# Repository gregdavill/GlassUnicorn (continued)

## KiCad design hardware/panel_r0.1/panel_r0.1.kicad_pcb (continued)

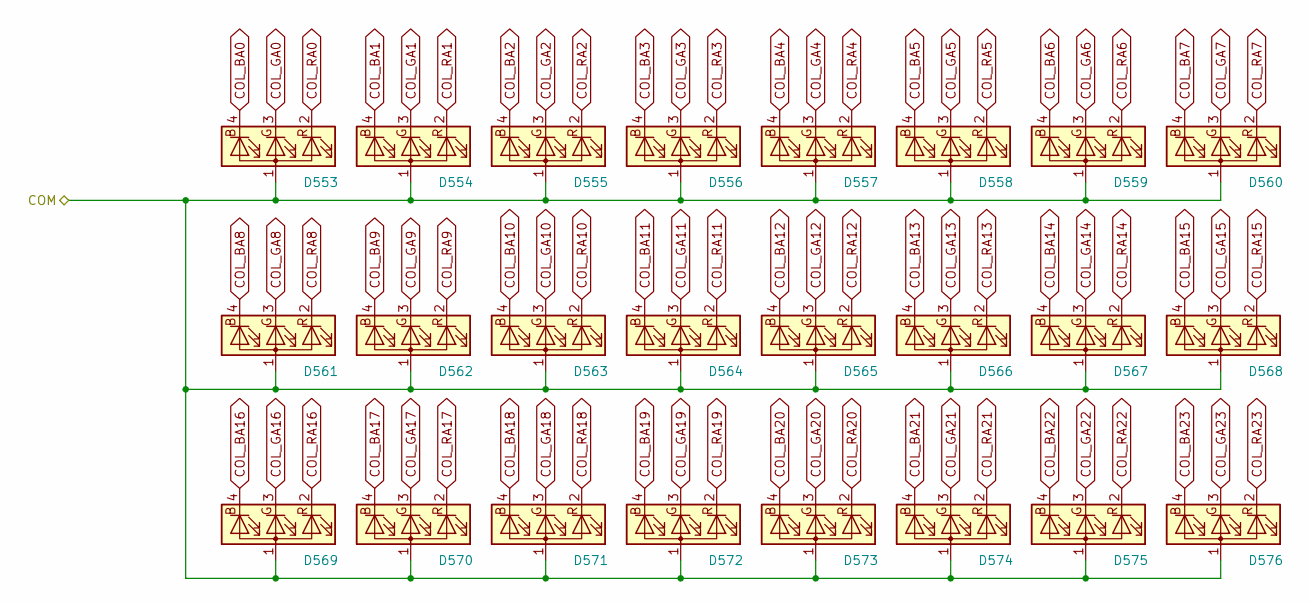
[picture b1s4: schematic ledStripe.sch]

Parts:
D1, D2, D3, D4, D5, D6, D7, D8, D9, D10, D11, D12, D13, D14, D15, D16, D17, D18, D19, D20, D21, D22, D23, D24: LED_ARGB; led_rbag_2121_dense

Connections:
/ledArray/sheet5D7371BF/COM: D1.1 (A), D2.1 (A), D3.1 (A), D4.1 (A), D5.1 (A), D6.1 (A), D7.1 (A), D8.1 (A), D9.1 (A), D10.1 (A), D11.1 (A), D12.1 (A), D13.1 (A), D14.1 (A), D15.1 (A), D16.1 (A), D17.1 (A), D18.1 (A), D19.1 (A), D20.1 (A), D21.1 (A), D22.1 (A), D23.1 (A), D24.1 (A); also elsewhere on the board
COL_BA0: D1.4 (BK); also elsewhere on the board
COL_BA1: D2.4 (BK); also elsewhere on the board
COL_BA2: D3.4 (BK); also elsewhere on the board
COL_BA3: D4.4 (BK); also elsewhere on the board
COL_BA4: D5.4 (BK); also elsewhere on the board
COL_BA5: D6.4 (BK); also elsewhere on the board
COL_BA6: D7.4 (BK); also elsewhere on the board
COL_BA7: D8.4 (BK); also elsewhere on the board
COL_BA8: D9.4 (BK); also elsewhere on the board
COL_BA9: D10.4 (BK); also elsewhere on the board
COL_BA10: D11.4 (BK); also elsewhere on the board
COL_BA11: D12.4 (BK); also elsewhere on the board
COL_BA12: D13.4 (BK); also elsewhere on the board
COL_BA13: D14.4 (BK); also elsewhere on the board
COL_BA14: D15.4 (BK); also elsewhere on the board
COL_BA15: D16.4 (BK); also elsewhere on the board
COL_BA16: D17.4 (BK); also elsewhere on the board
COL_BA17: D18.4 (BK); also elsewhere on the board
COL_BA18: D19.4 (BK); also elsewhere on the board
COL_BA19: D20.4 (BK); also elsewhere on the board
COL_BA20: D21.4 (BK); also elsewhere on the board
COL_BA21: D22.4 (BK); also elsewhere on the board
COL_BA22: D23.4 (BK); also elsewhere on the board
COL_BA23: D24.4 (BK); also elsewhere on the board
COL_GA0: D1.3 (GK); also elsewhere on the board
COL_GA1: D2.3 (GK); also elsewhere on the board
COL_GA2: D3.3 (GK); also elsewhere on the board
COL_GA3: D4.3 (GK); also elsewhere on the board
COL_GA4: D5.3 (GK); also elsewhere on the board
COL_GA5: D6.3 (GK); also elsewhere on the board
COL_GA6: D7.3 (GK); also elsewhere on the board
COL_GA7: D8.3 (GK); also elsewhere on the board
COL_GA8: D9.3 (GK); also elsewhere on the board
COL_GA9: D10.3 (GK); also elsewhere on the board
COL_GA10: D11.3 (GK); also elsewhere on the board
COL_GA11: D12.3 (GK); also elsewhere on the board
COL_GA12: D13.3 (GK); also elsewhere on the board
COL_GA13: D14.3 (GK); also elsewhere on the board
COL_GA14: D15.3 (GK); also elsewhere on the board
COL_GA15: D16.3 (GK); also elsewhere on the board
COL_GA16: D17.3 (GK); also elsewhere on the board
COL_GA17: D18.3 (GK); also elsewhere on the board
COL_GA18: D19.3 (GK); also elsewhere on the board
COL_GA19: D20.3 (GK); also elsewhere on the board
COL_GA20: D21.3 (GK); also elsewhere on the board
COL_GA21: D22.3 (GK); also elsewhere on the board
COL_GA22: D23.3 (GK); also elsewhere on the board
COL_GA23: D24.3 (GK); also elsewhere on the board
COL_RA0: D1.2 (RK); also elsewhere on the board
COL_RA1: D2.2 (RK); also elsewhere on the board
COL_RA2: D3.2 (RK); also elsewhere on the board
COL_RA3: D4.2 (RK); also elsewhere on the board
COL_RA4: D5.2 (RK); also elsewhere on the board
COL_RA5: D6.2 (RK); also elsewhere on the board
COL_RA6: D7.2 (RK); also elsewhere on the board
COL_RA7: D8.2 (RK); also elsewhere on the board
COL_RA8: D9.2 (RK); also elsewhere on the board
COL_RA9: D10.2 (RK); also elsewhere on the board
COL_RA10: D11.2 (RK); also elsewhere on the board
COL_RA11: D12.2 (RK); also elsewhere on the board
COL_RA12: D13.2 (RK); also elsewhere on the board
COL_RA13: D14.2 (RK); also elsewhere on the board
COL_RA14: D15.2 (RK); also elsewhere on the board
COL_RA15: D16.2 (RK); also elsewhere on the board
COL_RA16: D17.2 (RK); also elsewhere on the board
COL_RA17: D18.2 (RK); also elsewhere on the board
COL_RA18: D19.2 (RK); also elsewhere on the board
COL_RA19: D20.2 (RK); also elsewhere on the board
COL_RA20: D21.2 (RK); also elsewhere on the board
COL_RA21: D22.2 (RK); also elsewhere on the board
COL_RA22: D23.2 (RK); also elsewhere on the board
COL_RA23: D24.2 (RK); also elsewhere on the board

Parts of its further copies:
D25, D26, D27, D28, D29, D30, D31, D32, D33, D34, D35, D36, D37, D38, D39, D40, D41, D42, D43, D44, D45, D46, D47, D48, D49, D50, D51, D52, D53, D54, D55, D56, D57, D58, D59, D60, D61, D62, D63, D64, D65, D66, D67, D68, D69, D70, D71, D72, D73, D74, D75, D76, D77, D78, D79, D80, D81, D82, D83, D84, D85, D86, D87, D88, D89, D90, D91, D92, D93, D94, D95, D96, D97, D98, D99, D100, D101, D102, D103, D104, D105, D106, D107, D108, D109, D110, D111, D112, D113, D114, D115, D116, D117, D118, D119, D120, D121, D122, D123, D124, D125, D126, D127, D128, D129, D130, D131, D132, D133, D134, D135, D136, D137, D138, D139, D140, D141, D142, D143, D144, D145, D146, D147, D148, D149, D150, D151, D152, D153, D154, D155, D156, D157, D158, D159, D160, D161, D162, D163, D164, D165, D166, D167, D168, D169, D170, D171, D172, D173, D174, D175, D176, D177, D178, D179, D180, D181, D182, D183, D184, D185, D186, D187, D188, D189, D190, D191, D192, D193, D194, D195, D196, D197, D198, D199, D200, D201, D202, D203, D204, D205, D206, D207, D208, D209, D210, D211, D212, D213, D214, D215, D216, D217, D218, D219, D220, D221, D222, D223, D224, D225, D226, D227, D228, D229, D230, D231, D232, D233, D234, D235, D236, D237, D238, D239, D240, D241, D242, D243, D244, D245, D246, D247, D248, D249, D250, D251, D252, D253, D254, D255, D256, D257, D258, D259, D260, D261, D262, D263, D264, D265, D266, D267, D268, D269, D270, D271, D272, D273, D274, D275, D276, D277, D278, D279, D280, D281, D282, D283, D284, D285, D286, D287, D288, D289, D290, D291, D292, D293, D294, D295, D296, D297, D298, D299, D300, D301, D302, D303, D304, D305, D306, D307, D308, D309, D310, D311, D312, D313, D314, D315, D316, D317, D318, D319, D320, D321, D322, D323, D324, D325, D326, D327, D328, D329, D330, D331, D332, D333, D334, D335, D336, D337, D338, D339, D340, D341, D342, D343, D344, D345, D346, D347, D348, D349, D350, D351, D352, D353, D354, D355, D356, D357, D358, D359, D360, D361, D362, D363, D364, D365, D366, D367, D368, D369, D370, D371, D372, D373, D374, D375, D376, D377, D378, D379, D380, D381, D382, D383, D384, D385, D386, D387, D388, D389, D390, D391, D392, D393, D394, D395, D396, D397, D398, D399, D400, D401, D402, D403, D404, D405, D406, D407, D408, D409, D410, D411, D412, D413, D414, D415, D416, D417, D418, D419, D420, D421, D422, D423, D424, D425, D426, D427, D428, D429, D430, D431, D432, D433, D434, D435, D436, D437, D438, D439, D440, D441, D442, D443, D444, D445, D446, D447, D448, D449, D450, D451, D452, D453, D454, D455, D456, D457, D458, D459, D460, D461, D462, D463, D464, D465, D466, D467, D468, D469, D470, D471, D472, D473, D474, D475, D476, D477, D478, D479, D480, D481, D482, D483, D484, D485, D486, D487, D488, D489, D490, D491, D492, D493, D494, D495, D496, D497, D498, D499, D500, D501, D502, D503, D504, D505, D506, D507, D508, D509, D510, D511, D512, D513, D514, D515, D516, D517, D518, D519, D520, D521, D522, D523, D524, D525, D526, D527, D528, D529, D530, D531, D532, D533, D534, D535, D536, D537, D538, D539, D540, D541, D542, D543, D544, D545, D546, D547, D548, D549, D550, D551, D552, D553, D554, D555, D556, D557, D558, D559, D560, D561, D562, D563, D564, D565, D566, D567, D568, D569, D570, D571, D572, D573, D574, D575, D576: LED_ARGB; led_rbag_2121_dense

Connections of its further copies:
/ledArray/sheet5D7D53E6/COM: D193.1 (A), D194.1 (A), D195.1 (A), D196.1 (A), D197.1 (A), D198.1 (A), D199.1 (A), D200.1 (A), D201.1 (A), D202.1 (A), D203.1 (A), D204.1 (A), D205.1 (A), D206.1 (A), D207.1 (A), D208.1 (A), D209.1 (A), D210.1 (A), D211.1 (A), D212.1 (A), D213.1 (A), D214.1 (A), D215.1 (A), D216.1 (A); also elsewhere on the board
/ledArray/sheet5D7D53F6/COM: D217.1 (A), D218.1 (A), D219.1 (A), D220.1 (A), D221.1 (A), D222.1 (A), D223.1 (A), D224.1 (A), D225.1 (A), D226.1 (A), D227.1 (A), D228.1 (A), D229.1 (A), D230.1 (A), D231.1 (A), D232.1 (A), D233.1 (A), D234.1 (A), D235.1 (A), D236.1 (A), D237.1 (A), D238.1 (A), D239.1 (A), D240.1 (A); also elsewhere on the board
/ledArray/sheet5D7D542A/COM: D289.1 (A), D290.1 (A), D291.1 (A), D292.1 (A), D293.1 (A), D294.1 (A), D295.1 (A), D296.1 (A), D297.1 (A), D298.1 (A), D299.1 (A), D300.1 (A), D301.1 (A), D302.1 (A), D303.1 (A), D304.1 (A), D305.1 (A), D306.1 (A), D307.1 (A), D308.1 (A), D309.1 (A), D310.1 (A), D311.1 (A), D312.1 (A); also elsewhere on the board
/ledArray/sheet5D7D543A/COM: D313.1 (A), D314.1 (A), D315.1 (A), D316.1 (A), D317.1 (A), D318.1 (A), D319.1 (A), D320.1 (A), D321.1 (A), D322.1 (A), D323.1 (A), D324.1 (A), D325.1 (A), D326.1 (A), D327.1 (A), D328.1 (A), D329.1 (A), D330.1 (A), D331.1 (A), D332.1 (A), D333.1 (A), D334.1 (A), D335.1 (A), D336.1 (A); also elsewhere on the board
/ledArray/sheet5D7D544C/COM: D337.1 (A), D338.1 (A), D339.1 (A), D340.1 (A), D341.1 (A), D342.1 (A), D343.1 (A), D344.1 (A), D345.1 (A), D346.1 (A), D347.1 (A), D348.1 (A), D349.1 (A), D350.1 (A), D351.1 (A), D352.1 (A), D353.1 (A), D354.1 (A), D355.1 (A), D356.1 (A), D357.1 (A), D358.1 (A), D359.1 (A), D360.1 (A); also elsewhere on the board
/ledArray/sheet5D7D545C/COM: D361.1 (A), D362.1 (A), D363.1 (A), D364.1 (A), D365.1 (A), D366.1 (A), D367.1 (A), D368.1 (A), D369.1 (A), D370.1 (A), D371.1 (A), D372.1 (A), D373.1 (A), D374.1 (A), D375.1 (A), D376.1 (A), D377.1 (A), D378.1 (A), D379.1 (A), D380.1 (A), D381.1 (A), D382.1 (A), D383.1 (A), D384.1 (A); also elsewhere on the board
/ledArray/sheet5D7D5408/COM: D241.1 (A), D242.1 (A), D243.1 (A), D244.1 (A), D245.1 (A), D246.1 (A), D247.1 (A), D248.1 (A), D249.1 (A), D250.1 (A), D251.1 (A), D252.1 (A), D253.1 (A), D254.1 (A), D255.1 (A), D256.1 (A), D257.1 (A), D258.1 (A), D259.1 (A), D260.1 (A), D261.1 (A), D262.1 (A), D263.1 (A), D264.1 (A); also elsewhere on the board
/ledArray/sheet5D7D5419/COM: D265.1 (A), D266.1 (A), D267.1 (A), D268.1 (A), D269.1 (A), D270.1 (A), D271.1 (A), D272.1 (A), D273.1 (A), D274.1 (A), D275.1 (A), D276.1 (A), D277.1 (A), D278.1 (A), D279.1 (A), D280.1 (A), D281.1 (A), D282.1 (A), D283.1 (A), D284.1 (A), D285.1 (A), D286.1 (A), D287.1 (A), D288.1 (A); also elsewhere on the board
/ledArray/sheet5D82B2A6/COM: D457.1 (A), D458.1 (A), D459.1 (A), D460.1 (A), D461.1 (A), D462.1 (A), D463.1 (A), D464.1 (A), D465.1 (A), D466.1 (A), D467.1 (A), D468.1 (A), D469.1 (A), D470.1 (A), D471.1 (A), D472.1 (A), D473.1 (A), D474.1 (A), D475.1 (A), D476.1 (A), D477.1 (A), D478.1 (A), D479.1 (A), D480.1 (A); also elsewhere on the board
/ledArray/sheet5D82B2B7/COM: D481.1 (A), D482.1 (A), D483.1 (A), D484.1 (A), D485.1 (A), D486.1 (A), D487.1 (A), D488.1 (A), D489.1 (A), D490.1 (A), D491.1 (A), D492.1 (A), D493.1 (A), D494.1 (A), D495.1 (A), D496.1 (A), D497.1 (A), D498.1 (A), D499.1 (A), D500.1 (A), D501.1 (A), D502.1 (A), D503.1 (A), D504.1 (A); also elsewhere on the board
/ledArray/sheet5D82B2C7/COM: D505.1 (A), D506.1 (A), D507.1 (A), D508.1 (A), D509.1 (A), D510.1 (A), D511.1 (A), D512.1 (A), D513.1 (A), D514.1 (A), D515.1 (A), D516.1 (A), D517.1 (A), D518.1 (A), D519.1 (A), D520.1 (A), D521.1 (A), D522.1 (A), D523.1 (A), D524.1 (A), D525.1 (A), D526.1 (A), D527.1 (A), D528.1 (A); also elsewhere on the board
/ledArray/sheet5D82B2D9/COM: D529.1 (A), D530.1 (A), D531.1 (A), D532.1 (A), D533.1 (A), D534.1 (A), D535.1 (A), D536.1 (A), D537.1 (A), D538.1 (A), D539.1 (A), D540.1 (A), D541.1 (A), D542.1 (A), D543.1 (A), D544.1 (A), D545.1 (A), D546.1 (A), D547.1 (A), D548.1 (A), D549.1 (A), D550.1 (A), D551.1 (A), D552.1 (A); also elsewhere on the board
/ledArray/sheet5D82B2E9/COM: D553.1 (A), D554.1 (A), D555.1 (A), D556.1 (A), D557.1 (A), D558.1 (A), D559.1 (A), D560.1 (A), D561.1 (A), D562.1 (A), D563.1 (A), D564.1 (A), D565.1 (A), D566.1 (A), D567.1 (A), D568.1 (A), D569.1 (A), D570.1 (A), D571.1 (A), D572.1 (A), D573.1 (A), D574.1 (A), D575.1 (A), D576.1 (A); also elsewhere on the board
/ledArray/sheet5D82B273/COM: D385.1 (A), D386.1 (A), D387.1 (A), D388.1 (A), D389.1 (A), D390.1 (A), D391.1 (A), D392.1 (A), D393.1 (A), D394.1 (A), D395.1 (A), D396.1 (A), D397.1 (A), D398.1 (A), D399.1 (A), D400.1 (A), D401.1 (A), D402.1 (A), D403.1 (A), D404.1 (A), D405.1 (A), D406.1 (A), D407.1 (A), D408.1 (A); also elsewhere on the board
/ledArray/sheet5D82B283/COM: D409.1 (A), D410.1 (A), D411.1 (A), D412.1 (A), D413.1 (A), D414.1 (A), D415.1 (A), D416.1 (A), D417.1 (A), D418.1 (A), D419.1 (A), D420.1 (A), D421.1 (A), D422.1 (A), D423.1 (A), D424.1 (A), D425.1 (A), D426.1 (A), D427.1 (A), D428.1 (A), D429.1 (A), D430.1 (A), D431.1 (A), D432.1 (A); also elsewhere on the board
/ledArray/sheet5D82B295/COM: D433.1 (A), D434.1 (A), D435.1 (A), D436.1 (A), D437.1 (A), D438.1 (A), D439.1 (A), D440.1 (A), D441.1 (A), D442.1 (A), D443.1 (A), D444.1 (A), D445.1 (A), D446.1 (A), D447.1 (A), D448.1 (A), D449.1 (A), D450.1 (A), D451.1 (A), D452.1 (A), D453.1 (A), D454.1 (A), D455.1 (A), D456.1 (A); also elsewhere on the board
/ledArray/sheet5D7371D0/COM: D25.1 (A), D26.1 (A), D27.1 (A), D28.1 (A), D29.1 (A), D30.1 (A), D31.1 (A), D32.1 (A), D33.1 (A), D34.1 (A), D35.1 (A), D36.1 (A), D37.1 (A), D38.1 (A), D39.1 (A), D40.1 (A), D41.1 (A), D42.1 (A), D43.1 (A), D44.1 (A), D45.1 (A), D46.1 (A), D47.1 (A), D48.1 (A); also elsewhere on the board
/ledArray/sheet5D7371E3/COM: D49.1 (A), D50.1 (A), D51.1 (A), D52.1 (A), D53.1 (A), D54.1 (A), D55.1 (A), D56.1 (A), D57.1 (A), D58.1 (A), D59.1 (A), D60.1 (A), D61.1 (A), D62.1 (A), D63.1 (A), D64.1 (A), D65.1 (A), D66.1 (A), D67.1 (A), D68.1 (A), D69.1 (A), D70.1 (A), D71.1 (A), D72.1 (A); also elsewhere on the board
/ledArray/sheet5D7371F5/COM: D73.1 (A), D74.1 (A), D75.1 (A), D76.1 (A), D77.1 (A), D78.1 (A), D79.1 (A), D80.1 (A), D81.1 (A), D82.1 (A), D83.1 (A), D84.1 (A), D85.1 (A), D86.1 (A), D87.1 (A), D88.1 (A), D89.1 (A), D90.1 (A), D91.1 (A), D92.1 (A), D93.1 (A), D94.1 (A), D95.1 (A), D96.1 (A); also elsewhere on the board
/ledArray/sheet5D73722B/COM: D145.1 (A), D146.1 (A), D147.1 (A), D148.1 (A), D149.1 (A), D150.1 (A), D151.1 (A), D152.1 (A), D153.1 (A), D154.1 (A), D155.1 (A), D156.1 (A), D157.1 (A), D158.1 (A), D159.1 (A), D160.1 (A), D161.1 (A), D162.1 (A), D163.1 (A), D164.1 (A), D165.1 (A), D166.1 (A), D167.1 (A), D168.1 (A); also elsewhere on the board
/ledArray/sheet5D73723C/COM: D169.1 (A), D170.1 (A), D171.1 (A), D172.1 (A), D173.1 (A), D174.1 (A), D175.1 (A), D176.1 (A), D177.1 (A), D178.1 (A), D179.1 (A), D180.1 (A), D181.1 (A), D182.1 (A), D183.1 (A), D184.1 (A), D185.1 (A), D186.1 (A), D187.1 (A), D188.1 (A), D189.1 (A), D190.1 (A), D191.1 (A), D192.1 (A); also elsewhere on the board
/ledArray/sheet5D737207/COM: D97.1 (A), D98.1 (A), D99.1 (A), D100.1 (A), D101.1 (A), D102.1 (A), D103.1 (A), D104.1 (A), D105.1 (A), D106.1 (A), D107.1 (A), D108.1 (A), D109.1 (A), D110.1 (A), D111.1 (A), D112.1 (A), D113.1 (A), D114.1 (A), D115.1 (A), D116.1 (A), D117.1 (A), D118.1 (A), D119.1 (A), D120.1 (A); also elsewhere on the board
/ledArray/sheet5D737218/COM: D121.1 (A), D122.1 (A), D123.1 (A), D124.1 (A), D125.1 (A), D126.1 (A), D127.1 (A), D128.1 (A), D129.1 (A), D130.1 (A), D131.1 (A), D132.1 (A), D133.1 (A), D134.1 (A), D135.1 (A), D136.1 (A), D137.1 (A), D138.1 (A), D139.1 (A), D140.1 (A), D141.1 (A), D142.1 (A), D143.1 (A), D144.1 (A); also elsewhere on the board
COL_BA0: D25.4 (BK), D49.4 (BK), D73.4 (BK), D97.4 (BK), D121.4 (BK), D145.4 (BK), D169.4 (BK), D193.4 (BK), D217.4 (BK), D241.4 (BK), D265.4 (BK), D289.4 (BK), D313.4 (BK), D337.4 (BK), D361.4 (BK), D385.4 (BK), D409.4 (BK), D433.4 (BK), D457.4 (BK), D481.4 (BK), D505.4 (BK), D529.4 (BK), D553.4 (BK); also elsewhere on the board
COL_BA1: D26.4 (BK), D50.4 (BK), D74.4 (BK), D98.4 (BK), D122.4 (BK), D146.4 (BK), D170.4 (BK), D194.4 (BK), D218.4 (BK), D242.4 (BK), D266.4 (BK), D290.4 (BK), D314.4 (BK), D338.4 (BK), D362.4 (BK), D386.4 (BK), D410.4 (BK), D434.4 (BK), D458.4 (BK), D482.4 (BK), D506.4 (BK), D530.4 (BK), D554.4 (BK); also elsewhere on the board
COL_BA2: D27.4 (BK), D51.4 (BK), D75.4 (BK), D99.4 (BK), D123.4 (BK), D147.4 (BK), D171.4 (BK), D195.4 (BK), D219.4 (BK), D243.4 (BK), D267.4 (BK), D291.4 (BK), D315.4 (BK), D339.4 (BK), D363.4 (BK), D387.4 (BK), D411.4 (BK), D435.4 (BK), D459.4 (BK), D483.4 (BK), D507.4 (BK), D531.4 (BK), D555.4 (BK); also elsewhere on the board
COL_BA3: D28.4 (BK), D52.4 (BK), D76.4 (BK), D100.4 (BK), D124.4 (BK), D148.4 (BK), D172.4 (BK), D196.4 (BK), D220.4 (BK), D244.4 (BK), D268.4 (BK), D292.4 (BK), D316.4 (BK), D340.4 (BK), D364.4 (BK), D388.4 (BK), D412.4 (BK), D436.4 (BK), D460.4 (BK), D484.4 (BK), D508.4 (BK), D532.4 (BK), D556.4 (BK); also elsewhere on the board
COL_BA4: D29.4 (BK), D53.4 (BK), D77.4 (BK), D101.4 (BK), D125.4 (BK), D149.4 (BK), D173.4 (BK), D197.4 (BK), D221.4 (BK), D245.4 (BK), D269.4 (BK), D293.4 (BK), D317.4 (BK), D341.4 (BK), D365.4 (BK), D389.4 (BK), D413.4 (BK), D437.4 (BK), D461.4 (BK), D485.4 (BK), D509.4 (BK), D533.4 (BK), D557.4 (BK); also elsewhere on the board
COL_BA5: D30.4 (BK), D54.4 (BK), D78.4 (BK), D102.4 (BK), D126.4 (BK), D150.4 (BK), D174.4 (BK), D198.4 (BK), D222.4 (BK), D246.4 (BK), D270.4 (BK), D294.4 (BK), D318.4 (BK), D342.4 (BK), D366.4 (BK), D390.4 (BK), D414.4 (BK), D438.4 (BK), D462.4 (BK), D486.4 (BK), D510.4 (BK), D534.4 (BK), D558.4 (BK); also elsewhere on the board
COL_BA6: D31.4 (BK), D55.4 (BK), D79.4 (BK), D103.4 (BK), D127.4 (BK), D151.4 (BK), D175.4 (BK), D199.4 (BK), D223.4 (BK), D247.4 (BK), D271.4 (BK), D295.4 (BK), D319.4 (BK), D343.4 (BK), D367.4 (BK), D391.4 (BK), D415.4 (BK), D439.4 (BK), D463.4 (BK), D487.4 (BK), D511.4 (BK), D535.4 (BK), D559.4 (BK); also elsewhere on the board
COL_BA7: D32.4 (BK), D56.4 (BK), D80.4 (BK), D104.4 (BK), D128.4 (BK), D152.4 (BK), D176.4 (BK), D200.4 (BK), D224.4 (BK), D248.4 (BK), D272.4 (BK), D296.4 (BK), D320.4 (BK), D344.4 (BK), D368.4 (BK), D392.4 (BK), D416.4 (BK), D440.4 (BK), D464.4 (BK), D488.4 (BK), D512.4 (BK), D536.4 (BK), D560.4 (BK); also elsewhere on the board
COL_BA8: D33.4 (BK), D57.4 (BK), D81.4 (BK), D105.4 (BK), D129.4 (BK), D153.4 (BK), D177.4 (BK), D201.4 (BK), D225.4 (BK), D249.4 (BK), D273.4 (BK), D297.4 (BK), D321.4 (BK), D345.4 (BK), D369.4 (BK), D393.4 (BK), D417.4 (BK), D441.4 (BK), D465.4 (BK), D489.4 (BK), D513.4 (BK), D537.4 (BK), D561.4 (BK); also elsewhere on the board
COL_BA9: D34.4 (BK), D58.4 (BK), D82.4 (BK), D106.4 (BK), D130.4 (BK), D154.4 (BK), D178.4 (BK), D202.4 (BK), D226.4 (BK), D250.4 (BK), D274.4 (BK), D298.4 (BK), D322.4 (BK), D346.4 (BK), D370.4 (BK), D394.4 (BK), D418.4 (BK), D442.4 (BK), D466.4 (BK), D490.4 (BK), D514.4 (BK), D538.4 (BK), D562.4 (BK); also elsewhere on the board
COL_BA10: D35.4 (BK), D59.4 (BK), D83.4 (BK), D107.4 (BK), D131.4 (BK), D155.4 (BK), D179.4 (BK), D203.4 (BK), D227.4 (BK), D251.4 (BK), D275.4 (BK), D299.4 (BK), D323.4 (BK), D347.4 (BK), D371.4 (BK), D395.4 (BK), D419.4 (BK), D443.4 (BK), D467.4 (BK), D491.4 (BK), D515.4 (BK), D539.4 (BK), D563.4 (BK); also elsewhere on the board
COL_BA11: D36.4 (BK), D60.4 (BK), D84.4 (BK), D108.4 (BK), D132.4 (BK), D156.4 (BK), D180.4 (BK), D204.4 (BK), D228.4 (BK), D252.4 (BK), D276.4 (BK), D300.4 (BK), D324.4 (BK), D348.4 (BK), D372.4 (BK), D396.4 (BK), D420.4 (BK), D444.4 (BK), D468.4 (BK), D492.4 (BK), D516.4 (BK), D540.4 (BK), D564.4 (BK); also elsewhere on the board
COL_BA12: D37.4 (BK), D61.4 (BK), D85.4 (BK), D109.4 (BK), D133.4 (BK), D157.4 (BK), D181.4 (BK), D205.4 (BK), D229.4 (BK), D253.4 (BK), D277.4 (BK), D301.4 (BK), D325.4 (BK), D349.4 (BK), D373.4 (BK), D397.4 (BK), D421.4 (BK), D445.4 (BK), D469.4 (BK), D493.4 (BK), D517.4 (BK), D541.4 (BK), D565.4 (BK); also elsewhere on the board
COL_BA13: D38.4 (BK), D62.4 (BK), D86.4 (BK), D110.4 (BK), D134.4 (BK), D158.4 (BK), D182.4 (BK), D206.4 (BK), D230.4 (BK), D254.4 (BK), D278.4 (BK), D302.4 (BK), D326.4 (BK), D350.4 (BK), D374.4 (BK), D398.4 (BK), D422.4 (BK), D446.4 (BK), D470.4 (BK), D494.4 (BK), D518.4 (BK), D542.4 (BK), D566.4 (BK); also elsewhere on the board
COL_BA14: D39.4 (BK), D63.4 (BK), D87.4 (BK), D111.4 (BK), D135.4 (BK), D159.4 (BK), D183.4 (BK), D207.4 (BK), D231.4 (BK), D255.4 (BK), D279.4 (BK), D303.4 (BK), D327.4 (BK), D351.4 (BK), D375.4 (BK), D399.4 (BK), D423.4 (BK), D447.4 (BK), D471.4 (BK), D495.4 (BK), D519.4 (BK), D543.4 (BK), D567.4 (BK); also elsewhere on the board
COL_BA15: D40.4 (BK), D64.4 (BK), D88.4 (BK), D112.4 (BK), D136.4 (BK), D160.4 (BK), D184.4 (BK), D208.4 (BK), D232.4 (BK), D256.4 (BK), D280.4 (BK), D304.4 (BK), D328.4 (BK), D352.4 (BK), D376.4 (BK), D400.4 (BK), D424.4 (BK), D448.4 (BK), D472.4 (BK), D496.4 (BK), D520.4 (BK), D544.4 (BK), D568.4 (BK); also elsewhere on the board
COL_BA16: D41.4 (BK), D65.4 (BK), D89.4 (BK), D113.4 (BK), D137.4 (BK), D161.4 (BK), D185.4 (BK), D209.4 (BK), D233.4 (BK), D257.4 (BK), D281.4 (BK), D305.4 (BK), D329.4 (BK), D353.4 (BK), D377.4 (BK), D401.4 (BK), D425.4 (BK), D449.4 (BK), D473.4 (BK), D497.4 (BK), D521.4 (BK), D545.4 (BK), D569.4 (BK); also elsewhere on the board
COL_BA17: D42.4 (BK), D66.4 (BK), D90.4 (BK), D114.4 (BK), D138.4 (BK), D162.4 (BK), D186.4 (BK), D210.4 (BK), D234.4 (BK), D258.4 (BK), D282.4 (BK), D306.4 (BK), D330.4 (BK), D354.4 (BK), D378.4 (BK), D402.4 (BK), D426.4 (BK), D450.4 (BK), D474.4 (BK), D498.4 (BK), D522.4 (BK), D546.4 (BK), D570.4 (BK); also elsewhere on the board
COL_BA18: D43.4 (BK), D67.4 (BK), D91.4 (BK), D115.4 (BK), D139.4 (BK), D163.4 (BK), D187.4 (BK), D211.4 (BK), D235.4 (BK), D259.4 (BK), D283.4 (BK), D307.4 (BK), D331.4 (BK), D355.4 (BK), D379.4 (BK), D403.4 (BK), D427.4 (BK), D451.4 (BK), D475.4 (BK), D499.4 (BK), D523.4 (BK), D547.4 (BK), D571.4 (BK); also elsewhere on the board
COL_BA19: D44.4 (BK), D68.4 (BK), D92.4 (BK), D116.4 (BK), D140.4 (BK), D164.4 (BK), D188.4 (BK), D212.4 (BK), D236.4 (BK), D260.4 (BK), D284.4 (BK), D308.4 (BK), D332.4 (BK), D356.4 (BK), D380.4 (BK), D404.4 (BK), D428.4 (BK), D452.4 (BK), D476.4 (BK), D500.4 (BK), D524.4 (BK), D548.4 (BK), D572.4 (BK); also elsewhere on the board
COL_BA20: D45.4 (BK), D69.4 (BK), D93.4 (BK), D117.4 (BK), D141.4 (BK), D165.4 (BK), D189.4 (BK), D213.4 (BK), D237.4 (BK), D261.4 (BK), D285.4 (BK), D309.4 (BK), D333.4 (BK), D357.4 (BK), D381.4 (BK), D405.4 (BK), D429.4 (BK), D453.4 (BK), D477.4 (BK), D501.4 (BK), D525.4 (BK), D549.4 (BK), D573.4 (BK); also elsewhere on the board
COL_BA21: D46.4 (BK), D70.4 (BK), D94.4 (BK), D118.4 (BK), D142.4 (BK), D166.4 (BK), D190.4 (BK), D214.4 (BK), D238.4 (BK), D262.4 (BK), D286.4 (BK), D310.4 (BK), D334.4 (BK), D358.4 (BK), D382.4 (BK), D406.4 (BK), D430.4 (BK), D454.4 (BK), D478.4 (BK), D502.4 (BK), D526.4 (BK), D550.4 (BK), D574.4 (BK); also elsewhere on the board
COL_BA22: D47.4 (BK), D71.4 (BK), D95.4 (BK), D119.4 (BK), D143.4 (BK), D167.4 (BK), D191.4 (BK), D215.4 (BK), D239.4 (BK), D263.4 (BK), D287.4 (BK), D311.4 (BK), D335.4 (BK), D359.4 (BK), D383.4 (BK), D407.4 (BK), D431.4 (BK), D455.4 (BK), D479.4 (BK), D503.4 (BK), D527.4 (BK), D551.4 (BK), D575.4 (BK); also elsewhere on the board
COL_BA23: D48.4 (BK), D72.4 (BK), D96.4 (BK), D120.4 (BK), D144.4 (BK), D168.4 (BK), D192.4 (BK), D216.4 (BK), D240.4 (BK), D264.4 (BK), D288.4 (BK), D312.4 (BK), D336.4 (BK), D360.4 (BK), D384.4 (BK), D408.4 (BK), D432.4 (BK), D456.4 (BK), D480.4 (BK), D504.4 (BK), D528.4 (BK), D552.4 (BK), D576.4 (BK); also elsewhere on the board
COL_GA0: D25.3 (GK), D49.3 (GK), D73.3 (GK), D97.3 (GK), D121.3 (GK), D145.3 (GK), D169.3 (GK), D193.3 (GK), D217.3 (GK), D241.3 (GK), D265.3 (GK), D289.3 (GK), D313.3 (GK), D337.3 (GK), D361.3 (GK), D385.3 (GK), D409.3 (GK), D433.3 (GK), D457.3 (GK), D481.3 (GK), D505.3 (GK), D529.3 (GK), D553.3 (GK); also elsewhere on the board
COL_GA1: D26.3 (GK), D50.3 (GK), D74.3 (GK), D98.3 (GK), D122.3 (GK), D146.3 (GK), D170.3 (GK), D194.3 (GK), D218.3 (GK), D242.3 (GK), D266.3 (GK), D290.3 (GK), D314.3 (GK), D338.3 (GK), D362.3 (GK), D386.3 (GK), D410.3 (GK), D434.3 (GK), D458.3 (GK), D482.3 (GK), D506.3 (GK), D530.3 (GK), D554.3 (GK); also elsewhere on the board
COL_GA2: D27.3 (GK), D51.3 (GK), D75.3 (GK), D99.3 (GK), D123.3 (GK), D147.3 (GK), D171.3 (GK), D195.3 (GK), D219.3 (GK), D243.3 (GK), D267.3 (GK), D291.3 (GK), D315.3 (GK), D339.3 (GK), D363.3 (GK), D387.3 (GK), D411.3 (GK), D435.3 (GK), D459.3 (GK), D483.3 (GK), D507.3 (GK), D531.3 (GK), D555.3 (GK); also elsewhere on the board
COL_GA3: D28.3 (GK), D52.3 (GK), D76.3 (GK), D100.3 (GK), D124.3 (GK), D148.3 (GK), D172.3 (GK), D196.3 (GK), D220.3 (GK), D244.3 (GK), D268.3 (GK), D292.3 (GK), D316.3 (GK), D340.3 (GK), D364.3 (GK), D388.3 (GK), D412.3 (GK), D436.3 (GK), D460.3 (GK), D484.3 (GK), D508.3 (GK), D532.3 (GK), D556.3 (GK); also elsewhere on the board
COL_GA4: D29.3 (GK), D53.3 (GK), D77.3 (GK), D101.3 (GK), D125.3 (GK), D149.3 (GK), D173.3 (GK), D197.3 (GK), D221.3 (GK), D245.3 (GK), D269.3 (GK), D293.3 (GK), D317.3 (GK), D341.3 (GK), D365.3 (GK), D389.3 (GK), D413.3 (GK), D437.3 (GK), D461.3 (GK), D485.3 (GK), D509.3 (GK), D533.3 (GK), D557.3 (GK); also elsewhere on the board
COL_GA5: D30.3 (GK), D54.3 (GK), D78.3 (GK), D102.3 (GK), D126.3 (GK), D150.3 (GK), D174.3 (GK), D198.3 (GK), D222.3 (GK), D246.3 (GK), D270.3 (GK), D294.3 (GK), D318.3 (GK), D342.3 (GK), D366.3 (GK), D390.3 (GK), D414.3 (GK), D438.3 (GK), D462.3 (GK), D486.3 (GK), D510.3 (GK), D534.3 (GK), D558.3 (GK); also elsewhere on the board
COL_GA6: D31.3 (GK), D55.3 (GK), D79.3 (GK), D103.3 (GK), D127.3 (GK), D151.3 (GK), D175.3 (GK), D199.3 (GK), D223.3 (GK), D247.3 (GK), D271.3 (GK), D295.3 (GK), D319.3 (GK), D343.3 (GK), D367.3 (GK), D391.3 (GK), D415.3 (GK), D439.3 (GK), D463.3 (GK), D487.3 (GK), D511.3 (GK), D535.3 (GK), D559.3 (GK); also elsewhere on the board
COL_GA7: D32.3 (GK), D56.3 (GK), D80.3 (GK), D104.3 (GK), D128.3 (GK), D152.3 (GK), D176.3 (GK), D200.3 (GK), D224.3 (GK), D248.3 (GK), D272.3 (GK), D296.3 (GK), D320.3 (GK), D344.3 (GK), D368.3 (GK), D392.3 (GK), D416.3 (GK), D440.3 (GK), D464.3 (GK), D488.3 (GK), D512.3 (GK), D536.3 (GK), D560.3 (GK); also elsewhere on the board
COL_GA8: D33.3 (GK), D57.3 (GK), D81.3 (GK), D105.3 (GK), D129.3 (GK), D153.3 (GK), D177.3 (GK), D201.3 (GK), D225.3 (GK), D249.3 (GK), D273.3 (GK), D297.3 (GK), D321.3 (GK), D345.3 (GK), D369.3 (GK), D393.3 (GK), D417.3 (GK), D441.3 (GK), D465.3 (GK), D489.3 (GK), D513.3 (GK), D537.3 (GK), D561.3 (GK); also elsewhere on the board
COL_GA9: D34.3 (GK), D58.3 (GK), D82.3 (GK), D106.3 (GK), D130.3 (GK), D154.3 (GK), D178.3 (GK), D202.3 (GK), D226.3 (GK), D250.3 (GK), D274.3 (GK), D298.3 (GK), D322.3 (GK), D346.3 (GK), D370.3 (GK), D394.3 (GK), D418.3 (GK), D442.3 (GK), D466.3 (GK), D490.3 (GK), D514.3 (GK), D538.3 (GK), D562.3 (GK); also elsewhere on the board
COL_GA10: D35.3 (GK), D59.3 (GK), D83.3 (GK), D107.3 (GK), D131.3 (GK), D155.3 (GK), D179.3 (GK), D203.3 (GK), D227.3 (GK), D251.3 (GK), D275.3 (GK), D299.3 (GK), D323.3 (GK), D347.3 (GK), D371.3 (GK), D395.3 (GK), D419.3 (GK), D443.3 (GK), D467.3 (GK), D491.3 (GK), D515.3 (GK), D539.3 (GK), D563.3 (GK); also elsewhere on the board
COL_GA11: D36.3 (GK), D60.3 (GK), D84.3 (GK), D108.3 (GK), D132.3 (GK), D156.3 (GK), D180.3 (GK), D204.3 (GK), D228.3 (GK), D252.3 (GK), D276.3 (GK), D300.3 (GK), D324.3 (GK), D348.3 (GK), D372.3 (GK), D396.3 (GK), D420.3 (GK), D444.3 (GK), D468.3 (GK), D492.3 (GK), D516.3 (GK), D540.3 (GK), D564.3 (GK); also elsewhere on the board
COL_GA12: D37.3 (GK), D61.3 (GK), D85.3 (GK), D109.3 (GK), D133.3 (GK), D157.3 (GK), D181.3 (GK), D205.3 (GK), D229.3 (GK), D253.3 (GK), D277.3 (GK), D301.3 (GK), D325.3 (GK), D349.3 (GK), D373.3 (GK), D397.3 (GK), D421.3 (GK), D445.3 (GK), D469.3 (GK), D493.3 (GK), D517.3 (GK), D541.3 (GK), D565.3 (GK); also elsewhere on the board
COL_GA13: D38.3 (GK), D62.3 (GK), D86.3 (GK), D110.3 (GK), D134.3 (GK), D158.3 (GK), D182.3 (GK), D206.3 (GK), D230.3 (GK), D254.3 (GK), D278.3 (GK), D302.3 (GK), D326.3 (GK), D350.3 (GK), D374.3 (GK), D398.3 (GK), D422.3 (GK), D446.3 (GK), D470.3 (GK), D494.3 (GK), D518.3 (GK), D542.3 (GK), D566.3 (GK); also elsewhere on the board
COL_GA14: D39.3 (GK), D63.3 (GK), D87.3 (GK), D111.3 (GK), D135.3 (GK), D159.3 (GK), D183.3 (GK), D207.3 (GK), D231.3 (GK), D255.3 (GK), D279.3 (GK), D303.3 (GK), D327.3 (GK), D351.3 (GK), D375.3 (GK), D399.3 (GK), D423.3 (GK), D447.3 (GK), D471.3 (GK), D495.3 (GK), D519.3 (GK), D543.3 (GK), D567.3 (GK); also elsewhere on the board
COL_GA15: D40.3 (GK), D64.3 (GK), D88.3 (GK), D112.3 (GK), D136.3 (GK), D160.3 (GK), D184.3 (GK), D208.3 (GK), D232.3 (GK), D256.3 (GK), D280.3 (GK), D304.3 (GK), D328.3 (GK), D352.3 (GK), D376.3 (GK), D400.3 (GK), D424.3 (GK), D448.3 (GK), D472.3 (GK), D496.3 (GK), D520.3 (GK), D544.3 (GK), D568.3 (GK); also elsewhere on the board
COL_GA16: D41.3 (GK), D65.3 (GK), D89.3 (GK), D113.3 (GK), D137.3 (GK), D161.3 (GK), D185.3 (GK), D209.3 (GK), D233.3 (GK), D257.3 (GK), D281.3 (GK), D305.3 (GK), D329.3 (GK), D353.3 (GK), D377.3 (GK), D401.3 (GK), D425.3 (GK), D449.3 (GK), D473.3 (GK), D497.3 (GK), D521.3 (GK), D545.3 (GK), D569.3 (GK); also elsewhere on the board
COL_GA17: D42.3 (GK), D66.3 (GK), D90.3 (GK), D114.3 (GK), D138.3 (GK), D162.3 (GK), D186.3 (GK), D210.3 (GK), D234.3 (GK), D258.3 (GK), D282.3 (GK), D306.3 (GK), D330.3 (GK), D354.3 (GK), D378.3 (GK), D402.3 (GK), D426.3 (GK), D450.3 (GK), D474.3 (GK), D498.3 (GK), D522.3 (GK), D546.3 (GK), D570.3 (GK); also elsewhere on the board
COL_GA18: D43.3 (GK), D67.3 (GK), D91.3 (GK), D115.3 (GK), D139.3 (GK), D163.3 (GK), D187.3 (GK), D211.3 (GK), D235.3 (GK), D259.3 (GK), D283.3 (GK), D307.3 (GK), D331.3 (GK), D355.3 (GK), D379.3 (GK), D403.3 (GK), D427.3 (GK), D451.3 (GK), D475.3 (GK), D499.3 (GK), D523.3 (GK), D547.3 (GK), D571.3 (GK); also elsewhere on the board
COL_GA19: D44.3 (GK), D68.3 (GK), D92.3 (GK), D116.3 (GK), D140.3 (GK), D164.3 (GK), D188.3 (GK), D212.3 (GK), D236.3 (GK), D260.3 (GK), D284.3 (GK), D308.3 (GK), D332.3 (GK), D356.3 (GK), D380.3 (GK), D404.3 (GK), D428.3 (GK), D452.3 (GK), D476.3 (GK), D500.3 (GK), D524.3 (GK), D548.3 (GK), D572.3 (GK); also elsewhere on the board
COL_GA20: D45.3 (GK), D69.3 (GK), D93.3 (GK), D117.3 (GK), D141.3 (GK), D165.3 (GK), D189.3 (GK), D213.3 (GK), D237.3 (GK), D261.3 (GK), D285.3 (GK), D309.3 (GK), D333.3 (GK), D357.3 (GK), D381.3 (GK), D405.3 (GK), D429.3 (GK), D453.3 (GK), D477.3 (GK), D501.3 (GK), D525.3 (GK), D549.3 (GK), D573.3 (GK); also elsewhere on the board
COL_GA21: D46.3 (GK), D70.3 (GK), D94.3 (GK), D118.3 (GK), D142.3 (GK), D166.3 (GK), D190.3 (GK), D214.3 (GK), D238.3 (GK), D262.3 (GK), D286.3 (GK), D310.3 (GK), D334.3 (GK), D358.3 (GK), D382.3 (GK), D406.3 (GK), D430.3 (GK), D454.3 (GK), D478.3 (GK), D502.3 (GK), D526.3 (GK), D550.3 (GK), D574.3 (GK); also elsewhere on the board
COL_GA22: D47.3 (GK), D71.3 (GK), D95.3 (GK), D119.3 (GK), D143.3 (GK), D167.3 (GK), D191.3 (GK), D215.3 (GK), D239.3 (GK), D263.3 (GK), D287.3 (GK), D311.3 (GK), D335.3 (GK), D359.3 (GK), D383.3 (GK), D407.3 (GK), D431.3 (GK), D455.3 (GK), D479.3 (GK), D503.3 (GK), D527.3 (GK), D551.3 (GK), D575.3 (GK); also elsewhere on the board
COL_GA23: D48.3 (GK), D72.3 (GK), D96.3 (GK), D120.3 (GK), D144.3 (GK), D168.3 (GK), D192.3 (GK), D216.3 (GK), D240.3 (GK), D264.3 (GK), D288.3 (GK), D312.3 (GK), D336.3 (GK), D360.3 (GK), D384.3 (GK), D408.3 (GK), D432.3 (GK), D456.3 (GK), D480.3 (GK), D504.3 (GK), D528.3 (GK), D552.3 (GK), D576.3 (GK); also elsewhere on the board
COL_RA0: D25.2 (RK), D49.2 (RK), D73.2 (RK), D97.2 (RK), D121.2 (RK), D145.2 (RK), D169.2 (RK), D193.2 (RK), D217.2 (RK), D241.2 (RK), D265.2 (RK), D289.2 (RK), D313.2 (RK), D337.2 (RK), D361.2 (RK), D385.2 (RK), D409.2 (RK), D433.2 (RK), D457.2 (RK), D481.2 (RK), D505.2 (RK), D529.2 (RK), D553.2 (RK); also elsewhere on the board
COL_RA1: D26.2 (RK), D50.2 (RK), D74.2 (RK), D98.2 (RK), D122.2 (RK), D146.2 (RK), D170.2 (RK), D194.2 (RK), D218.2 (RK), D242.2 (RK), D266.2 (RK), D290.2 (RK), D314.2 (RK), D338.2 (RK), D362.2 (RK), D386.2 (RK), D410.2 (RK), D434.2 (RK), D458.2 (RK), D482.2 (RK), D506.2 (RK), D530.2 (RK), D554.2 (RK); also elsewhere on the board
COL_RA2: D27.2 (RK), D51.2 (RK), D75.2 (RK), D99.2 (RK), D123.2 (RK), D147.2 (RK), D171.2 (RK), D195.2 (RK), D219.2 (RK), D243.2 (RK), D267.2 (RK), D291.2 (RK), D315.2 (RK), D339.2 (RK), D363.2 (RK), D387.2 (RK), D411.2 (RK), D435.2 (RK), D459.2 (RK), D483.2 (RK), D507.2 (RK), D531.2 (RK), D555.2 (RK); also elsewhere on the board
COL_RA3: D28.2 (RK), D52.2 (RK), D76.2 (RK), D100.2 (RK), D124.2 (RK), D148.2 (RK), D172.2 (RK), D196.2 (RK), D220.2 (RK), D244.2 (RK), D268.2 (RK), D292.2 (RK), D316.2 (RK), D340.2 (RK), D364.2 (RK), D388.2 (RK), D412.2 (RK), D436.2 (RK), D460.2 (RK), D484.2 (RK), D508.2 (RK), D532.2 (RK), D556.2 (RK); also elsewhere on the board
COL_RA4: D29.2 (RK), D53.2 (RK), D77.2 (RK), D101.2 (RK), D125.2 (RK), D149.2 (RK), D173.2 (RK), D197.2 (RK), D221.2 (RK), D245.2 (RK), D269.2 (RK), D293.2 (RK), D317.2 (RK), D341.2 (RK), D365.2 (RK), D389.2 (RK), D413.2 (RK), D437.2 (RK), D461.2 (RK), D485.2 (RK), D509.2 (RK), D533.2 (RK), D557.2 (RK); also elsewhere on the board
COL_RA5: D30.2 (RK), D54.2 (RK), D78.2 (RK), D102.2 (RK), D126.2 (RK), D150.2 (RK), D174.2 (RK), D198.2 (RK), D222.2 (RK), D246.2 (RK), D270.2 (RK), D294.2 (RK), D318.2 (RK), D342.2 (RK), D366.2 (RK), D390.2 (RK), D414.2 (RK), D438.2 (RK), D462.2 (RK), D486.2 (RK), D510.2 (RK), D534.2 (RK), D558.2 (RK); also elsewhere on the board
COL_RA6: D31.2 (RK), D55.2 (RK), D79.2 (RK), D103.2 (RK), D127.2 (RK), D151.2 (RK), D175.2 (RK), D199.2 (RK), D223.2 (RK), D247.2 (RK), D271.2 (RK), D295.2 (RK), D319.2 (RK), D343.2 (RK), D367.2 (RK), D391.2 (RK), D415.2 (RK), D439.2 (RK), D463.2 (RK), D487.2 (RK), D511.2 (RK), D535.2 (RK), D559.2 (RK); also elsewhere on the board
COL_RA7: D32.2 (RK), D56.2 (RK), D80.2 (RK), D104.2 (RK), D128.2 (RK), D152.2 (RK), D176.2 (RK), D200.2 (RK), D224.2 (RK), D248.2 (RK), D272.2 (RK), D296.2 (RK), D320.2 (RK), D344.2 (RK), D368.2 (RK), D392.2 (RK), D416.2 (RK), D440.2 (RK), D464.2 (RK), D488.2 (RK), D512.2 (RK), D536.2 (RK), D560.2 (RK); also elsewhere on the board
COL_RA8: D33.2 (RK), D57.2 (RK), D81.2 (RK), D105.2 (RK), D129.2 (RK), D153.2 (RK), D177.2 (RK), D201.2 (RK), D225.2 (RK), D249.2 (RK), D273.2 (RK), D297.2 (RK), D321.2 (RK), D345.2 (RK), D369.2 (RK), D393.2 (RK), D417.2 (RK), D441.2 (RK), D465.2 (RK), D489.2 (RK), D513.2 (RK), D537.2 (RK), D561.2 (RK); also elsewhere on the board
COL_RA9: D34.2 (RK), D58.2 (RK), D82.2 (RK), D106.2 (RK), D130.2 (RK), D154.2 (RK), D178.2 (RK), D202.2 (RK), D226.2 (RK), D250.2 (RK), D274.2 (RK), D298.2 (RK), D322.2 (RK), D346.2 (RK), D370.2 (RK), D394.2 (RK), D418.2 (RK), D442.2 (RK), D466.2 (RK), D490.2 (RK), D514.2 (RK), D538.2 (RK), D562.2 (RK); also elsewhere on the board
COL_RA10: D35.2 (RK), D59.2 (RK), D83.2 (RK), D107.2 (RK), D131.2 (RK), D155.2 (RK), D179.2 (RK), D203.2 (RK), D227.2 (RK), D251.2 (RK), D275.2 (RK), D299.2 (RK), D323.2 (RK), D347.2 (RK), D371.2 (RK), D395.2 (RK), D419.2 (RK), D443.2 (RK), D467.2 (RK), D491.2 (RK), D515.2 (RK), D539.2 (RK), D563.2 (RK); also elsewhere on the board
COL_RA11: D36.2 (RK), D60.2 (RK), D84.2 (RK), D108.2 (RK), D132.2 (RK), D156.2 (RK), D180.2 (RK), D204.2 (RK), D228.2 (RK), D252.2 (RK), D276.2 (RK), D300.2 (RK), D324.2 (RK), D348.2 (RK), D372.2 (RK), D396.2 (RK), D420.2 (RK), D444.2 (RK), D468.2 (RK), D492.2 (RK), D516.2 (RK), D540.2 (RK), D564.2 (RK); also elsewhere on the board
COL_RA12: D37.2 (RK), D61.2 (RK), D85.2 (RK), D109.2 (RK), D133.2 (RK), D157.2 (RK), D181.2 (RK), D205.2 (RK), D229.2 (RK), D253.2 (RK), D277.2 (RK), D301.2 (RK), D325.2 (RK), D349.2 (RK), D373.2 (RK), D397.2 (RK), D421.2 (RK), D445.2 (RK), D469.2 (RK), D493.2 (RK), D517.2 (RK), D541.2 (RK), D565.2 (RK); also elsewhere on the board
COL_RA13: D38.2 (RK), D62.2 (RK), D86.2 (RK), D110.2 (RK), D134.2 (RK), D158.2 (RK), D182.2 (RK), D206.2 (RK), D230.2 (RK), D254.2 (RK), D278.2 (RK), D302.2 (RK), D326.2 (RK), D350.2 (RK), D374.2 (RK), D398.2 (RK), D422.2 (RK), D446.2 (RK), D470.2 (RK), D494.2 (RK), D518.2 (RK), D542.2 (RK), D566.2 (RK); also elsewhere on the board
COL_RA14: D39.2 (RK), D63.2 (RK), D87.2 (RK), D111.2 (RK), D135.2 (RK), D159.2 (RK), D183.2 (RK), D207.2 (RK), D231.2 (RK), D255.2 (RK), D279.2 (RK), D303.2 (RK), D327.2 (RK), D351.2 (RK), D375.2 (RK), D399.2 (RK), D423.2 (RK), D447.2 (RK), D471.2 (RK), D495.2 (RK), D519.2 (RK), D543.2 (RK), D567.2 (RK); also elsewhere on the board
COL_RA15: D40.2 (RK), D64.2 (RK), D88.2 (RK), D112.2 (RK), D136.2 (RK), D160.2 (RK), D184.2 (RK), D208.2 (RK), D232.2 (RK), D256.2 (RK), D280.2 (RK), D304.2 (RK), D328.2 (RK), D352.2 (RK), D376.2 (RK), D400.2 (RK), D424.2 (RK), D448.2 (RK), D472.2 (RK), D496.2 (RK), D520.2 (RK), D544.2 (RK), D568.2 (RK); also elsewhere on the board
COL_RA16: D41.2 (RK), D65.2 (RK), D89.2 (RK), D113.2 (RK), D137.2 (RK), D161.2 (RK), D185.2 (RK), D209.2 (RK), D233.2 (RK), D257.2 (RK), D281.2 (RK), D305.2 (RK), D329.2 (RK), D353.2 (RK), D377.2 (RK), D401.2 (RK), D425.2 (RK), D449.2 (RK), D473.2 (RK), D497.2 (RK), D521.2 (RK), D545.2 (RK), D569.2 (RK); also elsewhere on the board
COL_RA17: D42.2 (RK), D66.2 (RK), D90.2 (RK), D114.2 (RK), D138.2 (RK), D162.2 (RK), D186.2 (RK), D210.2 (RK), D234.2 (RK), D258.2 (RK), D282.2 (RK), D306.2 (RK), D330.2 (RK), D354.2 (RK), D378.2 (RK), D402.2 (RK), D426.2 (RK), D450.2 (RK), D474.2 (RK), D498.2 (RK), D522.2 (RK), D546.2 (RK), D570.2 (RK); also elsewhere on the board
COL_RA18: D43.2 (RK), D67.2 (RK), D91.2 (RK), D115.2 (RK), D139.2 (RK), D163.2 (RK), D187.2 (RK), D211.2 (RK), D235.2 (RK), D259.2 (RK), D283.2 (RK), D307.2 (RK), D331.2 (RK), D355.2 (RK), D379.2 (RK), D403.2 (RK), D427.2 (RK), D451.2 (RK), D475.2 (RK), D499.2 (RK), D523.2 (RK), D547.2 (RK), D571.2 (RK); also elsewhere on the board
COL_RA19: D44.2 (RK), D68.2 (RK), D92.2 (RK), D116.2 (RK), D140.2 (RK), D164.2 (RK), D188.2 (RK), D212.2 (RK), D236.2 (RK), D260.2 (RK), D284.2 (RK), D308.2 (RK), D332.2 (RK), D356.2 (RK), D380.2 (RK), D404.2 (RK), D428.2 (RK), D452.2 (RK), D476.2 (RK), D500.2 (RK), D524.2 (RK), D548.2 (RK), D572.2 (RK); also elsewhere on the board
COL_RA20: D45.2 (RK), D69.2 (RK), D93.2 (RK), D117.2 (RK), D141.2 (RK), D165.2 (RK), D189.2 (RK), D213.2 (RK), D237.2 (RK), D261.2 (RK), D285.2 (RK), D309.2 (RK), D333.2 (RK), D357.2 (RK), D381.2 (RK), D405.2 (RK), D429.2 (RK), D453.2 (RK), D477.2 (RK), D501.2 (RK), D525.2 (RK), D549.2 (RK), D573.2 (RK); also elsewhere on the board
COL_RA21: D46.2 (RK), D70.2 (RK), D94.2 (RK), D118.2 (RK), D142.2 (RK), D166.2 (RK), D190.2 (RK), D214.2 (RK), D238.2 (RK), D262.2 (RK), D286.2 (RK), D310.2 (RK), D334.2 (RK), D358.2 (RK), D382.2 (RK), D406.2 (RK), D430.2 (RK), D454.2 (RK), D478.2 (RK), D502.2 (RK), D526.2 (RK), D550.2 (RK), D574.2 (RK); also elsewhere on the board
COL_RA22: D47.2 (RK), D71.2 (RK), D95.2 (RK), D119.2 (RK), D143.2 (RK), D167.2 (RK), D191.2 (RK), D215.2 (RK), D239.2 (RK), D263.2 (RK), D287.2 (RK), D311.2 (RK), D335.2 (RK), D359.2 (RK), D383.2 (RK), D407.2 (RK), D431.2 (RK), D455.2 (RK), D479.2 (RK), D503.2 (RK), D527.2 (RK), D551.2 (RK), D575.2 (RK); also elsewhere on the board
COL_RA23: D48.2 (RK), D72.2 (RK), D96.2 (RK), D120.2 (RK), D144.2 (RK), D168.2 (RK), D192.2 (RK), D216.2 (RK), D240.2 (RK), D264.2 (RK), D288.2 (RK), D312.2 (RK), D336.2 (RK), D360.2 (RK), D384.2 (RK), D408.2 (RK), D432.2 (RK), D456.2 (RK), D480.2 (RK), D504.2 (RK), D528.2 (RK), D552.2 (RK), D576.2 (RK); also elsewhere on the board
